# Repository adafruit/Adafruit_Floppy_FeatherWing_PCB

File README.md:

## Adafruit Floppy FeatherWing with 34-Pin IDC Connector PCB

<a href="http://www.adafruit.com/products/5679"><br/>
Click here to purchase one from the Adafruit shop</a>

PCB files for the Adafruit Floppy FeatherWing with 34-Pin IDC Connector. 

Format is EagleCAD schematic and board layout
* https://www.adafruit.com/product/5679

### Description

Relive the days when storage was counted out in kilo-bytes not giga-bytes, using the Adafruit Floppy FeatherWing on a Feather board - perfect for interfacing with 34-Pin IDC Connector floppy drives that were ubiquitous on PC's. This 'Wing has level shifting and a ready-to-plug connector that works with 3.5" or 5.25" floppy disks for reading or writing!

Floppy disks have an interesting data transfer method where raw bit transitions are measured and converted to data. This data streams pretty fast from the disk drive so you'll want to use a fast microcontroller that has large SRAM storage and ideally, a peripheral to DMA the data signal. For that reason we only have this FeatherWing working with the Feather M4 or Feather RP2040. ESP32, ATmega, nRF52, etc have not been ported to our support library!

Floppy disk drives require 5V power and logic. For the logic level shifting, we have a small boost converter on the 'Wing that will give 5V logic levels out the 34-pin connector. It will also shift the incoming signals down to a Feather-safe 3.3V.

For floppy driver powering you will likely need a separate external 5V power supply that can provide 5V at 2 A. You can't power most drives off of USB power, they have big motors that require more current than USB can provide!

We've got code and examples for three use cases:

Reading floppy disks and storing the raw bit patterns and/or converted data format for data archiving. For this use case we recommend using the 'Wing with a Feather programmed to act as a greaseweazle or fluxengine client device. Then run those command line programs on your computer to have the Feather send the raw track data to the computer for analysis, bit-repair and format interpretation. You can also write some formats via those two programs, for use with older computers. We also have a 'Write Disable' switch on board specifically for this use case so that it is not possible for the write-enable pin to accidentally be activated.
Reading/Writing FAT formatted floppy disks from Arduino, CircuitPython or a computer that is connected via USB. Floppy disks can still be used to save, read data from! This is great for retro-themed projects or if you want to write data to floppy disks for them to be used by IBM-PC compatibles or other devices that are expecting FAT-formatted floppy disks
Cool floppy music sequencing!
Each order comes with one FeatherWing with the 2x17 header attached and level shifting circuitry built in. Before it can be used to read/write floppies, you will need to:

Solder pin headers on to attach to a Feather board. 
Attach an M4 or RP2040 Feather as the driver/brains.
Find a 34-pin IDC Floppy Drive that works
Connect a 34-pin DC cable between the 'Wing and the Floppy drive.
Provide 5V power to the floppy drive, as much as 2 Amps. 5.25" disk drives will also need a 12V power supply!
Find some floppy disks to read/write
Many of these items are no longer sold, and will require some sleuthing to locate!

### License

Adafruit invests time and resources providing this open source design, please support Adafruit and open-source hardware by purchasing products from [Adafruit](https://www.adafruit.com)!

Designed by Limor Fried/Ladyada for Adafruit Industries.

Creative Commons Attribution/Share-Alike, all text above must be included in any redistribution. 
See license.txt for additional details.

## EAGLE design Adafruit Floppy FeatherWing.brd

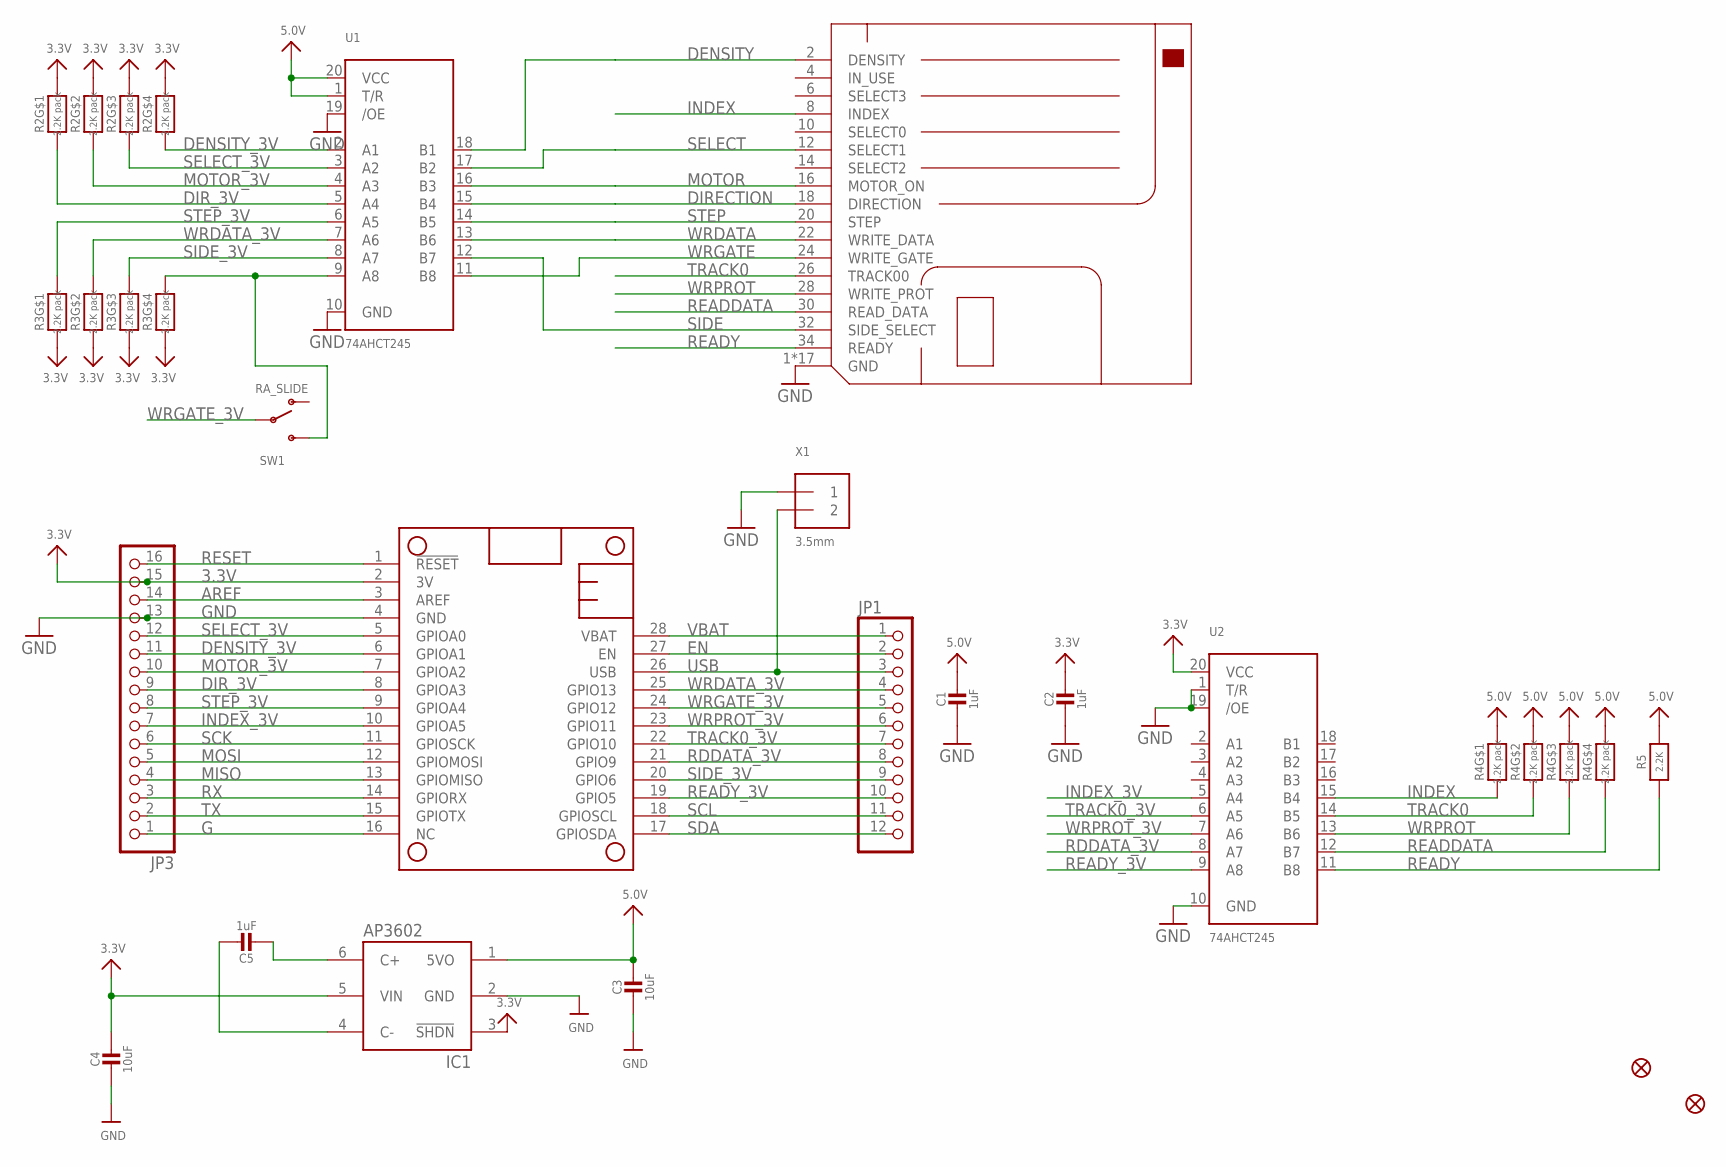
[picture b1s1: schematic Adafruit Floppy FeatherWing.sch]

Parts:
C1, C2, C5: 1uF; 0603-NO
C3, C4: 10uF; 0805-NO
FDD1: FLOPPY_IDC_SMT; 2X17_FLOPPY_SMTIDC
FID1, FID2: FIDUCIAL_1MM
IC1: AP3602; SOT23-6
JP1: HEADER-1X12; 1X12_ROUND
JP3: HEADER-1X16ROUND; 1X16_ROUND
MS1: FEATHERWING
R2, R3, R4: 2.2K pack; RESPACK_4X0603
R5: 2.2K; 0603-NO
SW1: RA_SLIDE; SPDT_SMT_SSSS811101
U1, U2: 74AHCT245; SSOP20
X1: 3.5mm; TERMBLOCK_1X2-3.5MM

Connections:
3.3V: C2.1, C4.1, IC1.3 (!SHDN), IC1.5 (VIN), JP3.15, MS1.2 (3V), R2.5 (2), R2.6 (2), R2.7 (2), R2.8 (2), R3.1, R3.2 (1), R3.3 (1), R3.4 (1), U2.20 (VCC)
5.0V: C1.1, C3.1, IC1.1 (5VO), R4.5 (2), R4.6 (2), R4.7 (2), R4.8 (2), R5.2, U1.1 (T/R), U1.20 (VCC)
AREF: JP3.14, MS1.3 (AREF)
DENSITY: FDD1.2 (DENSITY), U1.18 (B1)
DENSITY_3V: JP3.11, MS1.6 (GPIOA1), R2.4 (1), U1.2 (A1)
DIRECTION: FDD1.18 (DIRECTION), U1.15 (B4)
DIR_3V: JP3.9, MS1.8 (GPIOA3), R2.1, U1.5 (A4)
EN: JP1.2, MS1.27 (EN)
G: JP3.1, MS1.16 (NC)
GND: C1.2, C2.2, C3.2, C4.2, FDD1.1 (GND), FDD1.3 (GND), FDD1.5 (GND), FDD1.7 (GND), FDD1.9 (GND), FDD1.11 (GND), FDD1.13 (GND), FDD1.15 (GND), FDD1.17 (GND), FDD1.19 (GND), FDD1.21 (GND), FDD1.23 (GND), FDD1.25 (GND), FDD1.27 (GND), FDD1.29 (GND), FDD1.31 (GND), FDD1.33 (GND), IC1.2 (GND), JP3.13, MS1.4 (GND), U1.10 (GND), U1.19 (/OE), U2.1 (T/R), U2.10 (GND), U2.19 (/OE), X1.1
INDEX: FDD1.8 (INDEX), R4.1, U2.15 (B4)
INDEX_3V: JP3.7, MS1.10 (GPIOA5), U2.5 (A4)
MISO: JP3.4, MS1.13 (GPIOMISO)
MOSI: JP3.5, MS1.12 (GPIOMOSI)
MOTOR: FDD1.16 (MOTOR_ON), U1.16 (B3)
MOTOR_3V: JP3.10, MS1.7 (GPIOA2), R2.2 (1), U1.4 (A3)
unnamed: R3.5 (2), SW1.C (S), U1.9 (A8)
unnamed: C5.2, IC1.6 (C+)
unnamed: C5.1, IC1.4 (C-)
RDDATA_3V: JP1.8, MS1.21 (GPIO9), U2.8 (A7)
READDATA: FDD1.30 (READ_DATA), R4.4 (1), U2.12 (B7)
READY: FDD1.34 (READY), R5.1, U2.11 (B8)
READY_3V: JP1.10, MS1.19 (GPIO5), U2.9 (A8)
RESET: JP3.16, MS1.1 (!RESET)
RX: JP3.3, MS1.14 (GPIORX)
SCK: JP3.6, MS1.11 (GPIOSCK)
SCL: JP1.11, MS1.18 (GPIOSCL)
SDA: JP1.12, MS1.17 (GPIOSDA)
SELECT: FDD1.12 (SELECT1), U1.17 (B2)
SELECT_3V: JP3.12, MS1.5 (GPIOA0), R2.3 (1), U1.3 (A2)
SIDE: FDD1.32 (SIDE_SELECT), U1.12 (B7)
SIDE_3V: JP1.9, MS1.20 (GPIO6), R3.6 (2), U1.8 (A7)
STEP: FDD1.20 (STEP), U1.14 (B5)
STEP_3V: JP3.8, MS1.9 (GPIOA4), R3.8 (2), U1.6 (A5)
TRACK0: FDD1.26 (TRACK00), R4.2 (1), U2.14 (B5)
TRACK0_3V: JP1.7, MS1.22 (GPIO10), U2.6 (A5)
TX: JP3.2, MS1.15 (GPIOTX)
USB: JP1.3, MS1.26 (USB), X1.2
VBAT: JP1.1, MS1.28 (VBAT)
WRDATA: FDD1.22 (WRITE_DATA), U1.13 (B6)
WRDATA_3V: JP1.4, MS1.25 (GPIO13), R3.7 (2), U1.7 (A6)
WRGATE: FDD1.24 (WRITE_GATE), U1.11 (B8)
WRGATE_3V: JP1.5, MS1.24 (GPIO12), SW1.B
WRPROT: FDD1.28 (WRITE_PROT), R4.3 (1), U2.13 (B6)
WRPROT_3V: JP1.6, MS1.23 (GPIO11), U2.7 (A6)

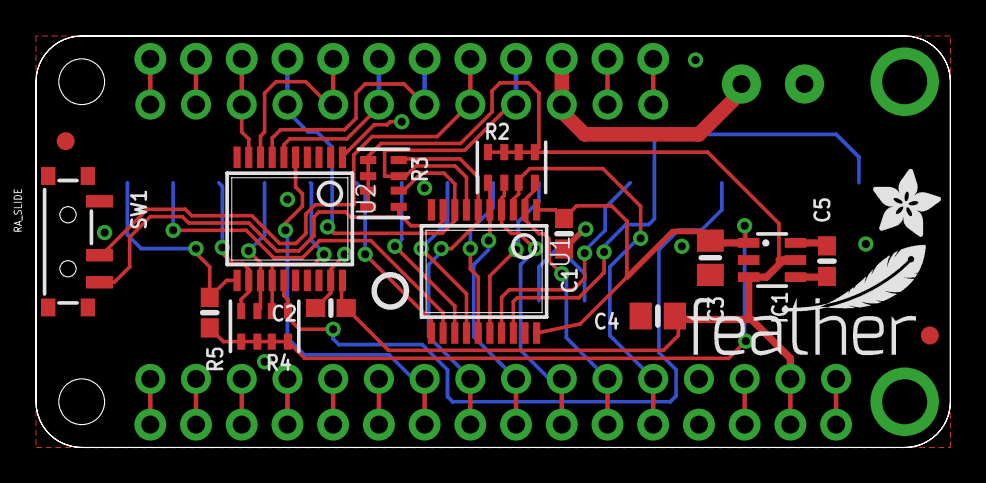
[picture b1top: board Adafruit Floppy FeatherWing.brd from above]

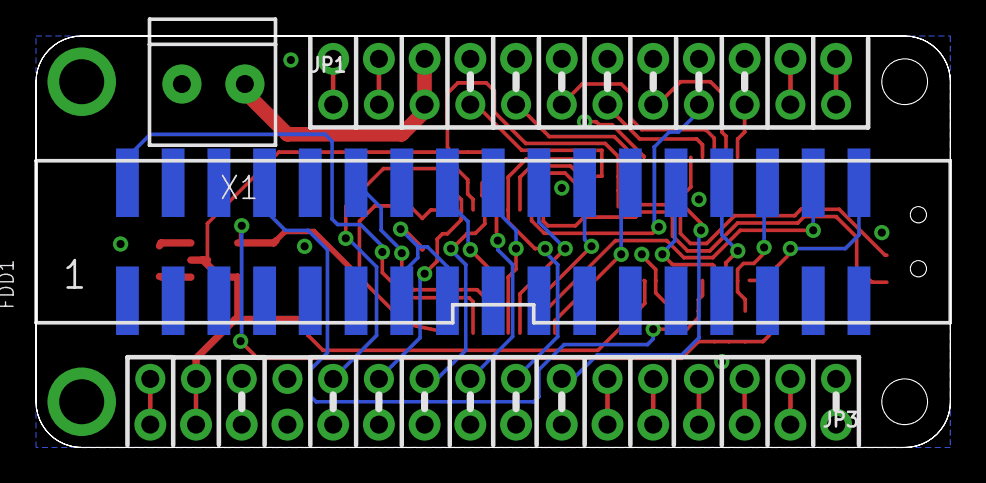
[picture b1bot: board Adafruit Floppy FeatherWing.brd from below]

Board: 2 copper layers, 50.8 x 22.9 mm, 59 parts (26 on the bottom side), 45 nets.

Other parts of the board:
PLABEL0: PLABEL0
PLABEL1: PLABEL1
PLABEL2: PLABEL2
PLABEL3: PLABEL3
PLABEL4: PLABEL4
PLABEL5: PLABEL5
PLABEL6: PLABEL6
PLABEL7: PLABEL7
PLABEL8: PLABEL8
PLABEL9: PLABEL9
PLABEL10: PLABEL10
PLABEL11: PLABEL11
PLABEL12: PLABEL12
PLABEL13: PLABEL13
PLABEL14: PLABEL14
PLABEL15: PLABEL15
PLABEL16: PLABEL16
PLABEL17: PLABEL17
PLABEL18: PLABEL18
PLABEL19: PLABEL19
PLABEL20: PLABEL20
PLABEL21: PLABEL21
PLABEL22: PLABEL22
PLABEL23: PLABEL23
PLABEL24: PLABEL24
PLABEL25: PLABEL25
PLABEL26: PLABEL26
PLABEL27: PLABEL27
PLABEL28: PLABEL28
PLABEL29: PLABEL29
PLABEL30: PLABEL30
PLABEL31: PLABEL31
PLABEL32: PLABEL32
PLABEL33: PLABEL33
PLABEL34: PLABEL34
PLABEL35: PLABEL35
U$26: PCBFEAT-REV-040
U$27: FEATHERLOGO_SMALL
U$28: ADAFRUIT_3.5MM

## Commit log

2023-02-21 cookiecutter output
